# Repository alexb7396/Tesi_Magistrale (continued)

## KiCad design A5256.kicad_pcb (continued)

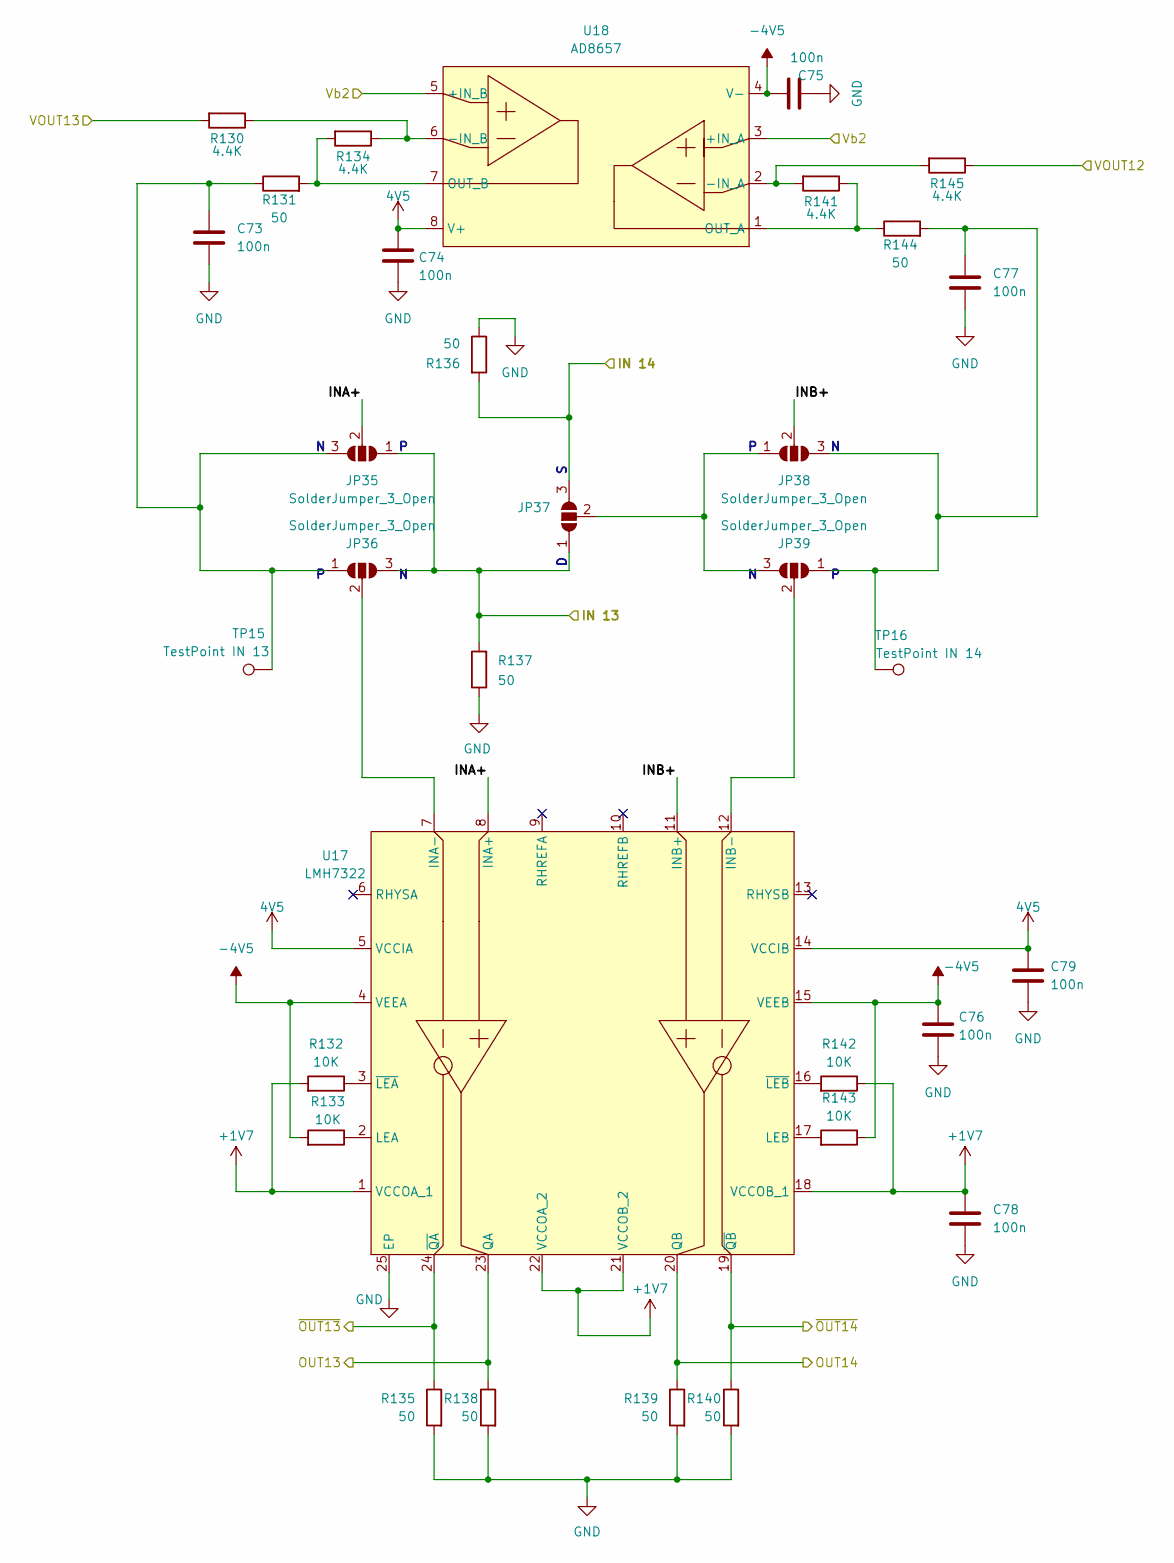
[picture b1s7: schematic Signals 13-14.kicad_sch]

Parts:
C73, C74, C75, C76, C77, C78, C79: 100n; C_0603_1608Metric_Pad1.08x0.95mm_HandSolder
JP35, JP36, JP37, JP38, JP39: SolderJumper_3_Open; SolderJumper-3_P1.3mm_Open_RoundedPad1.0x1.5mm_NumberLabels
R130, R134, R141, R145: 4.4K; R_0603_1608Metric_Pad0.98x0.95mm_HandSolder
R131, R135, R136, R137, R138, R139, R140, R144: 50; R_0603_1608Metric_Pad0.98x0.95mm_HandSolder
R132, R133, R142, R143: 10K; R_0603_1608Metric_Pad0.98x0.95mm_HandSolder
TP15: TestPoint IN 13; TestPoint_Pad_D1.0mm
TP16: TestPoint IN 14; TestPoint_Pad_D1.0mm
U17: LMH7322; QFN50P400X400X80-25N
U18: AD8657; SOP65P490X110-8N

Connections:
4V5: C74.1, C79.1, U17.5 (VCCIA), U17.14 (VCCIB), U18.8 (V+); also elsewhere on the board
+1V7: C78.1, R132.2, R142.1, U17.1 (VCCOA_1), U17.18 (VCCOB_1), U17.21 (VCCOB_2), U17.22 (VCCOA_2); also elsewhere on the board
-4V5: C75.1, C76.1, R133.2, R143.1, U17.4 (VEEA), U17.15 (VEEB), U18.4 (V-); also elsewhere on the board
/IN 13: JP35.1 (A), JP36.3 (B), JP37.1 (A), R137.2; also elsewhere on the board
/IN 14: JP37.3 (B), R136.2; also elsewhere on the board
/OUT13: R138.1, U17.23 (QA); also elsewhere on the board
/OUT14: R139.1, U17.20 (QB); also elsewhere on the board
/Signals 13-14/INA+: JP35.2 (C), U17.8 (INA+)
/Signals 13-14/INB+: JP38.2 (C), U17.11 (INB+)
/VOUT12: R145.1; also elsewhere on the board
/VOUT13: R130.2; also elsewhere on the board
/Vb2: U18.3 (+IN_A), U18.5 (+IN_B); also elsewhere on the board
/~OUT13: R135.1, U17.24 (~QA); also elsewhere on the board
/~OUT14: R140.1, U17.19 (~QB); also elsewhere on the board
GND: C73.2, C74.2, C75.2, C76.2, C77.2, C78.2, C79.2, R135.2, R136.1, R137.1, R138.2, R139.2, R140.2, U17.25 (EP); also elsewhere on the board
unnamed: C73.1, JP35.3 (B), JP36.1 (A), R131.1, TP15.1
unnamed: JP36.2 (C), U17.7 (INA-)
unnamed: JP37.2 (C), JP38.1 (A), JP39.3 (B)
unnamed: C77.1, JP38.3 (B), JP39.1 (A), R144.2, TP16.1
unnamed: JP39.2 (C), U17.12 (INB-)
unnamed: R133.1, U17.2 (LEA)
unnamed: R143.2, U17.17 (LEB)
unnamed: R132.1, U17.3 (~LEA)
unnamed: R142.2, U17.16 (~LEB)
unnamed: R141.2, R145.2, U18.2 (-IN_A)
unnamed: R130.1, R134.1, U18.6 (-IN_B)
unnamed: R141.1, R144.1, U18.1 (OUT_A)
unnamed: R131.2, R134.2, U18.7 (OUT_B)

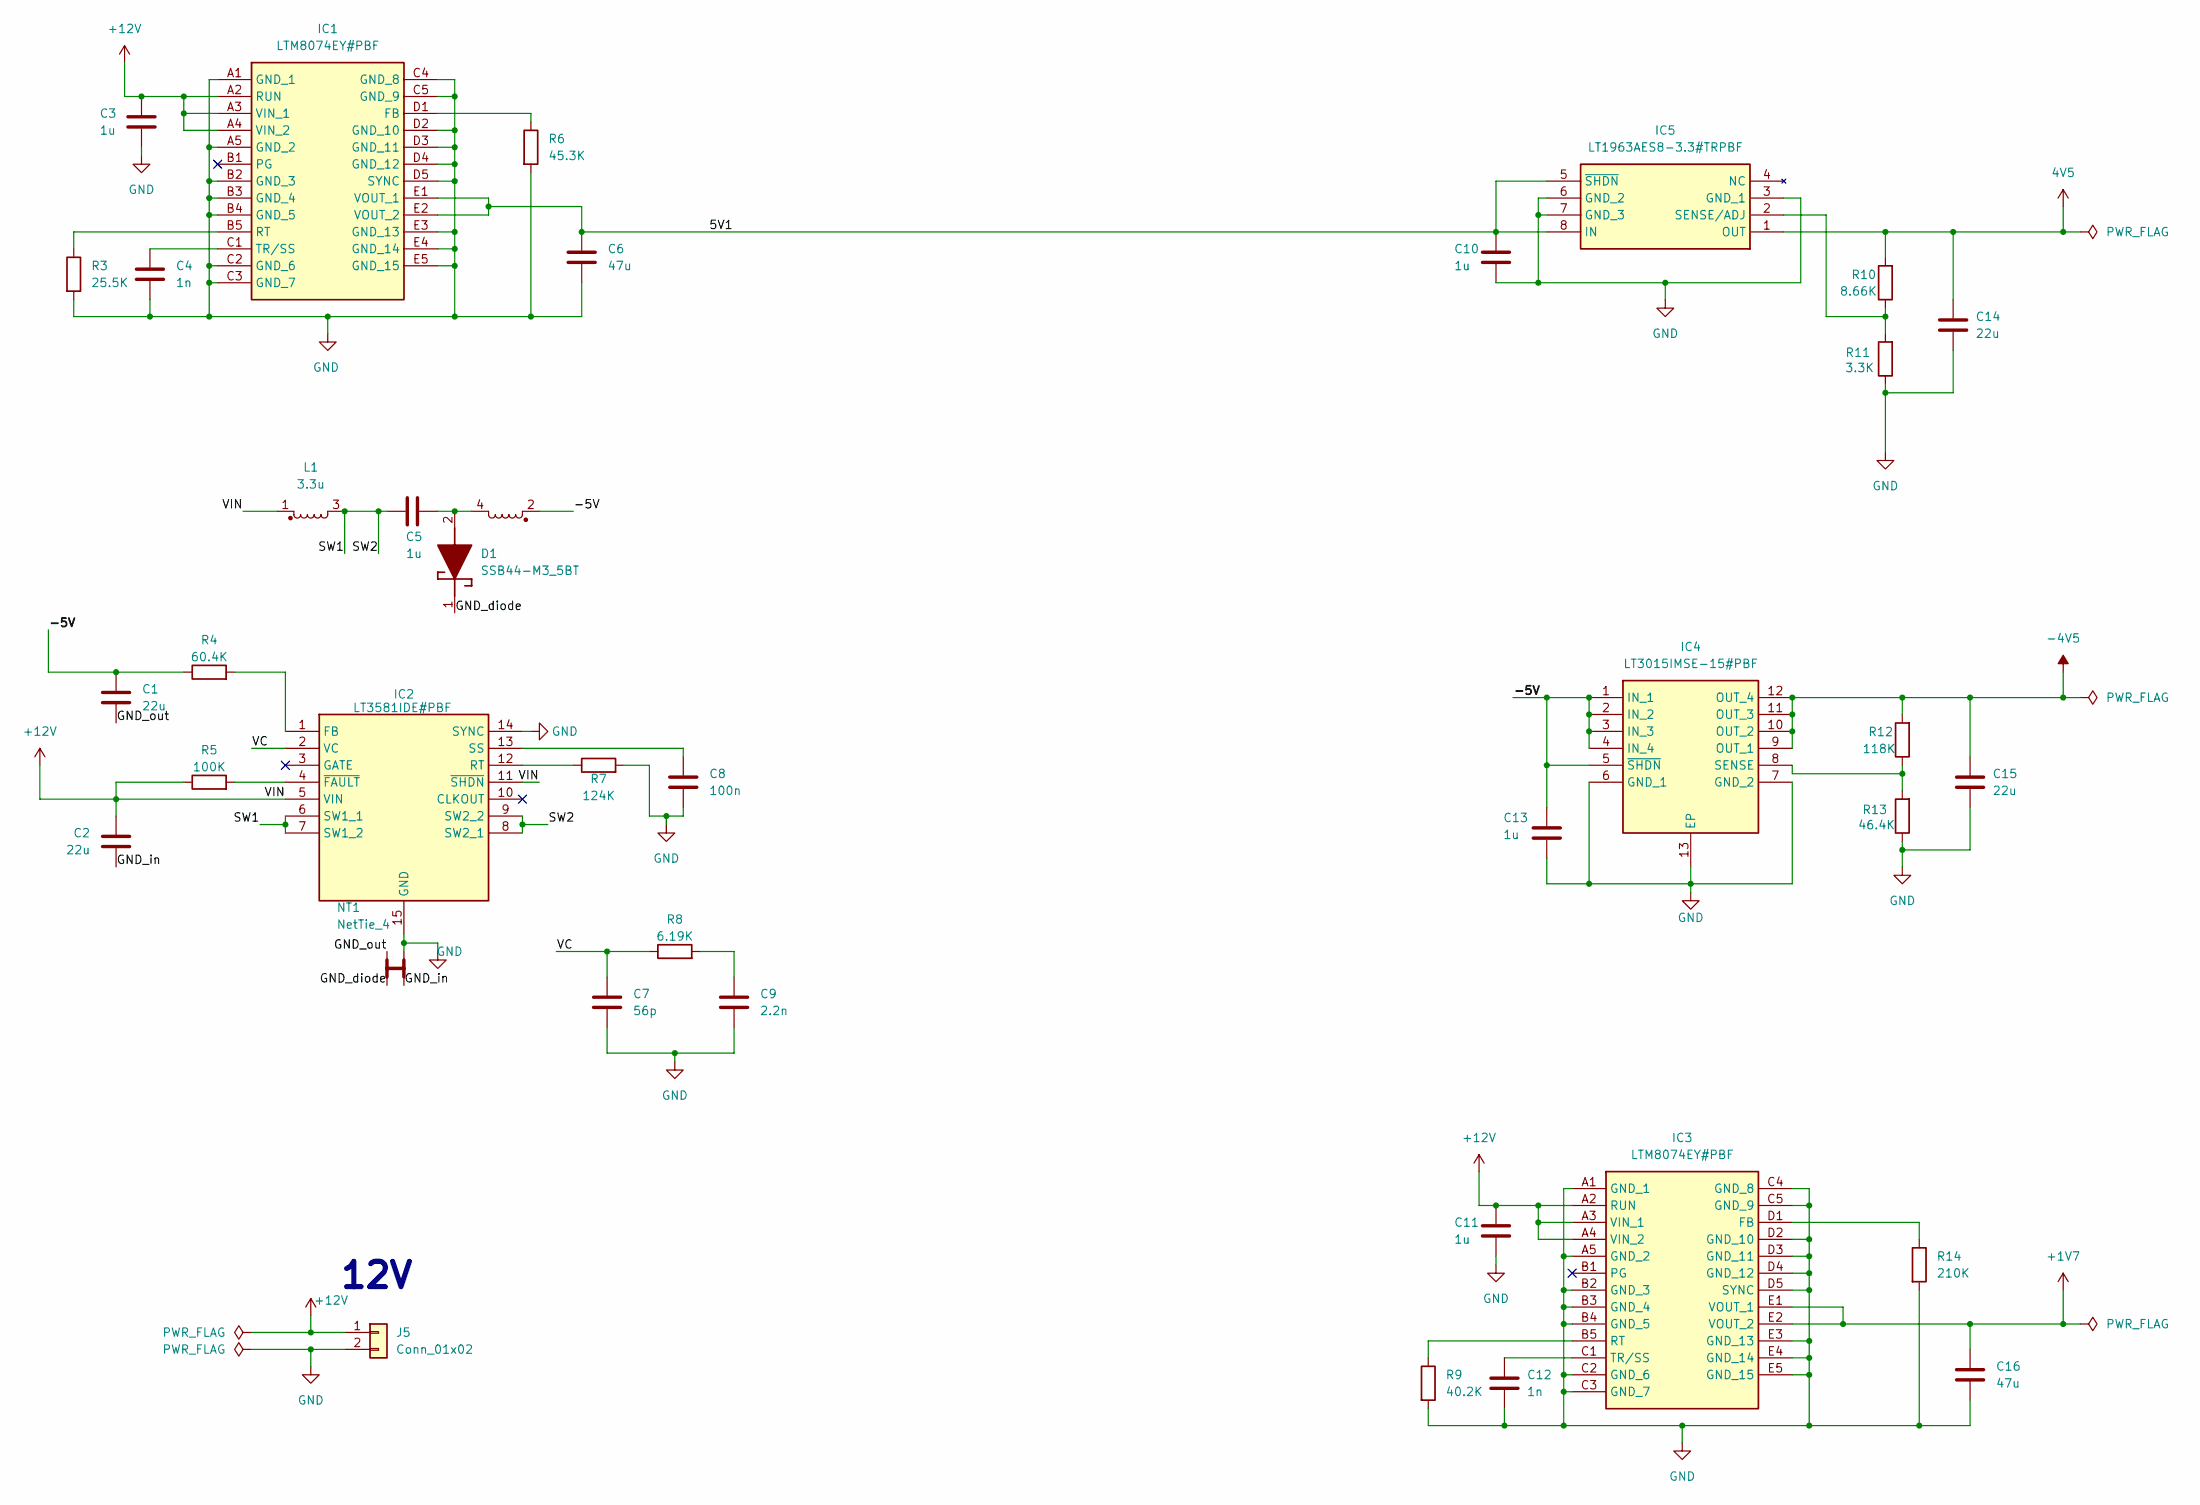
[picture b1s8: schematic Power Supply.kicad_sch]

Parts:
C1, C2: 22u; C_1210_3225Metric_Pad1.33x2.70mm_HandSolder
C3, C10, C11, C13: 1u; C_0603_1608Metric_Pad1.08x0.95mm_HandSolder
C4, C12: 1n; C_0603_1608Metric_Pad1.08x0.95mm_HandSolder
C5: 1u; C_1206_3216Metric_Pad1.33x1.80mm_HandSolder
C6, C16: 47u; C_0805_2012Metric_Pad1.18x1.45mm_HandSolder
C7: 56p; C_0603_1608Metric_Pad1.08x0.95mm_HandSolder
C8: 100n; C_0603_1608Metric_Pad1.08x0.95mm_HandSolder
C9: 2.2n; C_0603_1608Metric_Pad1.08x0.95mm_HandSolder
C14, C15: 22u; C_0805_2012Metric_Pad1.18x1.45mm_HandSolder
D1: SSB44-M3_5BT; DIOM5436X244N; Mouser Part Number 78-SSB44-M35BT
IC1, IC3: LTM8074EY#PBF; BGA25C65P5X5_400X400X198; Manufacturer_Part_Number LTM8074EY#PBF; Mouser Part Number 584-LTM8074EY#PBF
IC2: LT3581IDE#PBF; SON50P300X400X80-15N-D; Mouser Part Number 584-LT3581IDE#PBF
IC4: LT3015IMSE-15#PBF; SOP65P490X110-13N; Manufacturer_Part_Number LT3015IMSE-15#PBF; Mouser Part Number 584-LT3015IMSE-15PBF
IC5: LT1963AES8-3.3#TRPBF; SOIC127P599X175-8N; Manufacturer_Part_Number LT1963AES8-3.3#TRPBF; Mouser Part Number 584-1963AES8-3.3TPF
J5: Conn_01x02; 1725656
L1: 3.3u; MSD7342332MLC
NT1: NetTie_4; NetTie-4_SMD_Pad0.5mm
R3: 25.5K; R_0603_1608Metric_Pad0.98x0.95mm_HandSolder
R4: 60.4K; R_0603_1608Metric_Pad0.98x0.95mm_HandSolder
R5: 100K; R_0603_1608Metric_Pad0.98x0.95mm_HandSolder
R6: 45.3K; R_0603_1608Metric_Pad0.98x0.95mm_HandSolder
R7: 124K; R_0603_1608Metric_Pad0.98x0.95mm_HandSolder
R8: 6.19K; R_0603_1608Metric_Pad0.98x0.95mm_HandSolder
R9: 40.2K; R_0603_1608Metric_Pad0.98x0.95mm_HandSolder
R10: 8.66K; R_0603_1608Metric_Pad0.98x0.95mm_HandSolder
R11: 3.3K; R_0603_1608Metric_Pad0.98x0.95mm_HandSolder
R12: 118K; R_0603_1608Metric_Pad0.98x0.95mm_HandSolder
R13: 46.4K; R_0603_1608Metric_Pad0.98x0.95mm_HandSolder
R14: 210K; R_0603_1608Metric_Pad0.98x0.95mm_HandSolder

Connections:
4V5: C14.1, IC5.1 (OUT), R10.2; also elsewhere on the board
+1V7: C16.1, IC3.E1 (VOUT_1), IC3.E2 (VOUT_2); also elsewhere on the board
+12V: C2.1, C3.1, C11.1, IC1.A2 (RUN), IC1.A3 (VIN_1), IC1.A4 (VIN_2), IC2.5 (VIN), IC2.11 (~SHDN), IC3.A2 (RUN), IC3.A3 (VIN_1), IC3.A4 (VIN_2), J5.1, L1.1, R5.1
-4V5: C15.1, IC4.9 (OUT_1), IC4.10 (OUT_2), IC4.11 (OUT_3), IC4.12 (OUT_4), R12.2; also elsewhere on the board
/Power Supply/5V1: C6.1, C10.1, IC1.E1 (VOUT_1), IC1.E2 (VOUT_2), IC5.5 (~SHDN), IC5.8 (IN)
/Power Supply/-5V: C1.1, C13.1, IC4.1 (IN_1), IC4.2 (IN_2), IC4.3 (IN_3), IC4.4 (IN_4), IC4.5 (~SHDN), L1.2, R4.1
/Power Supply/GND_diode: D1.1 (K), NT1.1
/Power Supply/GND_in: C2.2, NT1.3
/Power Supply/GND_out: C1.2, NT1.2
/Power Supply/SW1: C5.2, IC2.6 (SW1_1), IC2.7 (SW1_2), IC2.8 (SW2_1), IC2.9 (SW2_2), L1.3
/Power Supply/VC: C7.2, IC2.2 (VC), R8.1
GND: C3.2, C4.2, C6.2, C7.1, C8.2, C9.2, C10.2, C11.2, C12.2, C13.2, C14.2, C15.2, C16.2, IC1.A1 (GND_1), IC1.A5 (GND_2), IC1.B2 (GND_3), IC1.B3 (GND_4), IC1.B4 (GND_5), IC1.C2 (GND_6), IC1.C3 (GND_7), IC1.C4 (GND_8), IC1.C5 (GND_9), IC1.D2 (GND_10), IC1.D3 (GND_11), IC1.D4 (GND_12), IC1.D5 (SYNC), IC1.E3 (GND_13), IC1.E4 (GND_14), IC1.E5 (GND_15), IC2.14 (SYNC), IC2.15 (GND), IC3.A1 (GND_1), IC3.A5 (GND_2), IC3.B2 (GND_3), IC3.B3 (GND_4), IC3.B4 (GND_5), IC3.C2 (GND_6), IC3.C3 (GND_7), IC3.C4 (GND_8), IC3.C5 (GND_9), IC3.D2 (GND_10), IC3.D3 (GND_11), IC3.D4 (GND_12), IC3.D5 (SYNC), IC3.E3 (GND_13), IC3.E4 (GND_14), IC3.E5 (GND_15), IC4.6 (GND_1), IC4.7 (GND_2), IC4.13 (EP), IC5.3 (GND_1), IC5.6 (GND_2), IC5.7 (GND_3), J5.2, NT1.4, R3.2, R6.2, R7.2, R9.2, R11.1, R13.1, R14.2; also elsewhere on the board
unnamed: C9.1, R8.2
unnamed: C5.1, D1.2 (A), L1.4
unnamed: IC1.D1 (FB), R6.1
unnamed: IC1.B5 (RT), R3.1
unnamed: C4.1, IC1.C1 (TR/SS)
unnamed: IC2.1 (FB), R4.2
unnamed: IC2.12 (RT), R7.1
unnamed: C8.1, IC2.13 (SS)
unnamed: IC2.4 (~FAULT), R5.2
unnamed: IC3.D1 (FB), R14.1
unnamed: IC3.B5 (RT), R9.1
unnamed: C12.1, IC3.C1 (TR/SS)
unnamed: IC4.8 (SENSE), R12.1, R13.2
unnamed: IC5.2 (SENSE/ADJ), R10.1, R11.2

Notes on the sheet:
12V

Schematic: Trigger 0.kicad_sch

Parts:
C17, C18, C19, C20, C21, C22, C24, C25, C26, C27, C28, C29, C30: 100n; C_0603_1608Metric_Pad1.08x0.95mm_HandSolder
C23: 470n; C_0603_1608Metric_Pad1.08x0.95mm_HandSolder
C80: 10u; C_0603_1608Metric_Pad1.08x0.95mm_HandSolder
IC6: AD5673RBCPZ-1; QFN40P400X400X100-29N-D; Manufacturer_Part_Number AD5673RBCPZ-1; Mouser Part Number 584-AD5673RBCPZ-1
JP1, JP2, JP3, JP4: SolderJumper_3_Open; SolderJumper-3_P1.3mm_Open_RoundedPad1.0x1.5mm_NumberLabels
L2: 22u; L_0603_1608Metric_Pad1.05x0.95mm_HandSolder
R15, R16, R19, R20, R22, R24, R31, R32, R33: 50; R_0603_1608Metric_Pad0.98x0.95mm_HandSolder
R17: 3K; R_0603_1608Metric_Pad0.98x0.95mm_HandSolder
R18: 1K; R_0603_1608Metric_Pad0.98x0.95mm_HandSolder
R21, R23, R29, R30: 4.4K; R_0603_1608Metric_Pad0.98x0.95mm_HandSolder
R25, R26, R27, R28: 10K; R_0603_1608Metric_Pad0.98x0.95mm_HandSolder
TP1: TestPoint IN 0A; TestPoint_Pad_D1.0mm
TP2: TestPoint IN 0B; TestPoint_Pad_D1.0mm
U1: LTC2627IDE-1_PBF; DFN-12_DE; MANUFACTURER_PART_NUMBER ltc2627ide1
U2, U3: AD8657; SOP65P490X110-8N
U4: LMH7322; QFN50P400X400X80-25N

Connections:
4V5: C18.1, C19.1, C22.1, C27.1, C28.1, C80.1, IC6.2 (VDD), IC6.17 (~LDAC), IC6.18 (VLOGIC), IC6.20 (~RESET), JP1.1 (A), JP2.1 (A), JP3.3 (B), JP4.3 (B), U1.3 (*LDAC), U1.8 (VCC), U2.8 (V+), U3.8 (V+), U4.5 (VCCIA), U4.14 (VCCIB); also elsewhere on the board
+1V7: C25.1, R27.2, R28.1, U4.1 (VCCOA_1), U4.18 (VCCOB_1), U4.21 (VCCOB_2), U4.22 (VCCOA_2); also elsewhere on the board
-4V5: C20.1, C24.1, C26.1, R25.2, R26.1, U2.4 (V-), U3.4 (V-), U4.4 (VEEA), U4.15 (VEEB); also elsewhere on the board
/CH0/A0: IC6.4 (A0), JP4.2 (C)
/CH0/A1: IC6.5 (A1), JP2.2 (C)
/CH0/CA0: JP3.2 (C), U1.1 (CA0)
/CH0/CA1: JP1.2 (C), U1.2 (CA1)
/CH0/SCL: IC6.3 (SCL), U1.4 (SCL); also elsewhere on the board
/CH0/SDA: IC6.19 (SDA), U1.5 (SDA); also elsewhere on the board
/CH0/Vb: C23.1, R17.2, R18.2, U2.3 (+IN_A), U2.5 (+IN_B)
/IN 0: R33.2, U4.7 (INA-), U4.12 (INB-); also elsewhere on the board
/QA_CH0: R22.1, U4.23 (QA); also elsewhere on the board
/QB_CH0: R20.1, U4.20 (QB); also elsewhere on the board
/VOUT0: IC6.25 (VOUT8); also elsewhere on the board
/VOUT1: IC6.24 (VOUT9); also elsewhere on the board
/VOUT2: IC6.27 (VOUT2); also elsewhere on the board
/VOUT3: IC6.26 (VOUT3); also elsewhere on the board
/VOUT4: IC6.1 (VOUT0); also elsewhere on the board
/VOUT5: IC6.28 (VOUT1); also elsewhere on the board
/VOUT6: IC6.7 (VOUT7); also elsewhere on the board
/VOUT7: IC6.8 (VOUT6); also elsewhere on the board
/VOUT8: IC6.9 (VOUT5); also elsewhere on the board
/VOUT9: IC6.10 (VOUT4); also elsewhere on the board
/VOUT10: IC6.13 (VOUT13); also elsewhere on the board
/VOUT11: IC6.14 (VOUT12); also elsewhere on the board
/VOUT12: IC6.22 (VOUT11); also elsewhere on the board
/VOUT13: IC6.23 (VOUT10); also elsewhere on the board
/Vb1: C21.1, R16.1, U3.3 (+IN_A), U3.5 (+IN_B); also elsewhere on the board
/Vb2: C17.1, R15.1; also elsewhere on the board
/~QA_CH0: R24.1, U4.24 (~QA); also elsewhere on the board
/~QB_CH0: R19.1, U4.19 (~QB); also elsewhere on the board
GND: C17.2, C18.2, C19.2, C20.2, C21.2, C22.2, C23.2, C24.2, C25.2, C26.2, C27.2, C28.2, C29.2, C30.2, C80.2, IC6.6 (GAIN), IC6.15 (GND_1), IC6.16 (GND_2), IC6.29 (EPAD), JP1.3 (B), JP2.3 (B), JP3.1 (A), JP4.1 (A), L2.2, R19.2, R20.2, R22.2, R24.2, R33.1, U1.6 (CA2), U1.10 (GND), U1.11 (REFLO), U1.13 (EPAD), U4.25 (EP); also elsewhere on the board
unnamed: IC6.21 (VREF), R17.1, U1.9 (REF)
unnamed: L2.1, R18.1
unnamed: R21.1, U1.12 (VOUTA)
unnamed: R30.2, U1.7 (VOUTB)
unnamed: R16.2, U2.1 (OUT_A), U2.2 (-IN_A)
unnamed: R15.2, U2.6 (-IN_B), U2.7 (OUT_B)
unnamed: R21.2, R23.1, U3.2 (-IN_A)
unnamed: R29.2, R30.1, U3.6 (-IN_B)
unnamed: R23.2, R31.1, U3.1 (OUT_A)
unnamed: R29.1, R32.1, U3.7 (OUT_B)
unnamed: C30.1, R32.2, TP2.1, U4.8 (INA+)
unnamed: C29.1, R31.2, TP1.1, U4.11 (INB+)
unnamed: R26.2, U4.2 (LEA)
unnamed: R25.1, U4.17 (LEB)
unnamed: R28.2, U4.3 (~LEA)
unnamed: R27.1, U4.16 (~LEB)

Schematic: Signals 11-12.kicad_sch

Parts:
C66, C67, C68, C69, C70, C71, C72: 100n; C_0603_1608Metric_Pad1.08x0.95mm_HandSolder
JP30, JP31, JP32, JP33, JP34: SolderJumper_3_Open; SolderJumper-3_P1.3mm_Open_RoundedPad1.0x1.5mm_NumberLabels
R114, R118, R125, R129: 4.4K; R_0603_1608Metric_Pad0.98x0.95mm_HandSolder
R115, R119, R120, R121, R122, R123, R124, R128: 50; R_0603_1608Metric_Pad0.98x0.95mm_HandSolder
R116, R117, R126, R127: 10K; R_0603_1608Metric_Pad0.98x0.95mm_HandSolder
TP13: TestPoint IN 11; TestPoint_Pad_D1.0mm
TP14: TestPoint IN 12; TestPoint_Pad_D1.0mm
U15: LMH7322; QFN50P400X400X80-25N
U16: AD8657; SOP65P490X110-8N

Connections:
4V5: C67.1, C72.1, U15.5 (VCCIA), U15.14 (VCCIB), U16.8 (V+); also elsewhere on the board
+1V7: C71.1, R116.2, R126.1, U15.1 (VCCOA_1), U15.18 (VCCOB_1), U15.21 (VCCOB_2), U15.22 (VCCOA_2); also elsewhere on the board
-4V5: C68.1, C69.1, R117.2, R127.1, U15.4 (VEEA), U15.15 (VEEB), U16.4 (V-); also elsewhere on the board
/IN 11: JP30.1 (A), JP31.3 (B), JP32.1 (A), R121.2; also elsewhere on the board
/IN 12: JP32.3 (B), R120.2; also elsewhere on the board
/OUT11: R122.1, U15.23 (QA); also elsewhere on the board
/OUT12: R123.1, U15.20 (QB); also elsewhere on the board
/Signals 11-12/INA+: JP30.2 (C), U15.8 (INA+)
/Signals 11-12/INB+: JP33.2 (C), U15.11 (INB+)
/VOUT10: R129.1; also elsewhere on the board
/VOUT11: R114.2; also elsewhere on the board
/Vb2: U16.3 (+IN_A), U16.5 (+IN_B); also elsewhere on the board
/~OUT11: R119.1, U15.24 (~QA); also elsewhere on the board
/~OUT12: R124.1, U15.19 (~QB); also elsewhere on the board
GND: C66.2, C67.2, C68.2, C69.2, C70.2, C71.2, C72.2, R119.2, R120.1, R121.1, R122.2, R123.2, R124.2, U15.25 (EP); also elsewhere on the board
unnamed: C66.1, JP30.3 (B), JP31.1 (A), R115.1, TP13.1
unnamed: JP31.2 (C), U15.7 (INA-)
unnamed: JP32.2 (C), JP33.1 (A), JP34.3 (B)
unnamed: C70.1, JP33.3 (B), JP34.1 (A), R128.2, TP14.1
unnamed: JP34.2 (C), U15.12 (INB-)
unnamed: R117.1, U15.2 (LEA)
unnamed: R127.2, U15.17 (LEB)
unnamed: R116.1, U15.3 (~LEA)
unnamed: R126.2, U15.16 (~LEB)
unnamed: R125.2, R129.2, U16.2 (-IN_A)
unnamed: R114.1, R118.1, U16.6 (-IN_B)
unnamed: R125.1, R128.1, U16.1 (OUT_A)
unnamed: R115.2, R118.2, U16.7 (OUT_B)

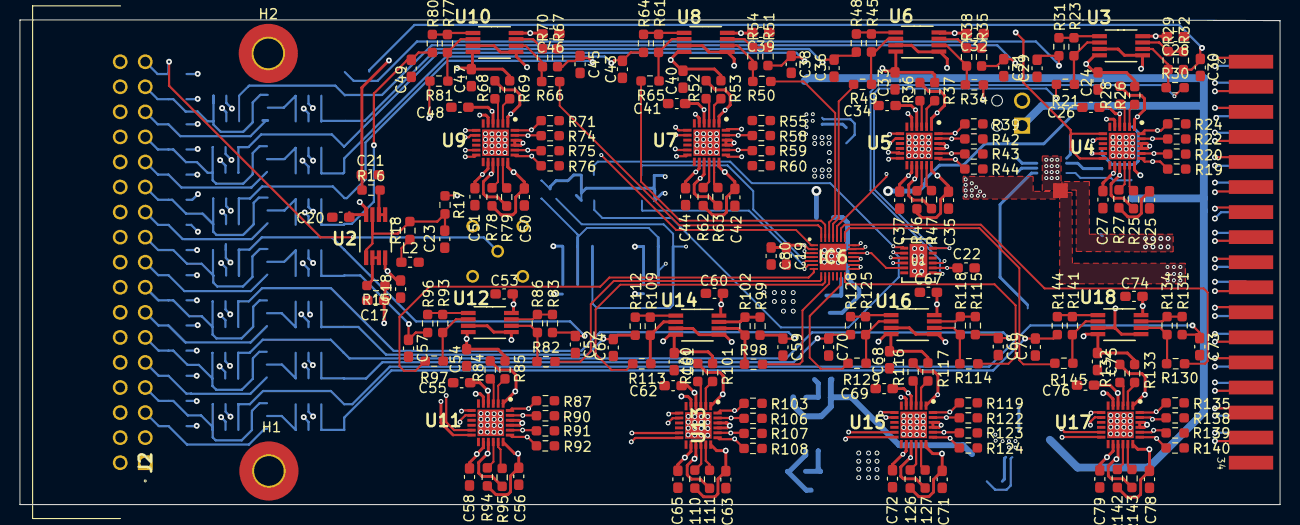
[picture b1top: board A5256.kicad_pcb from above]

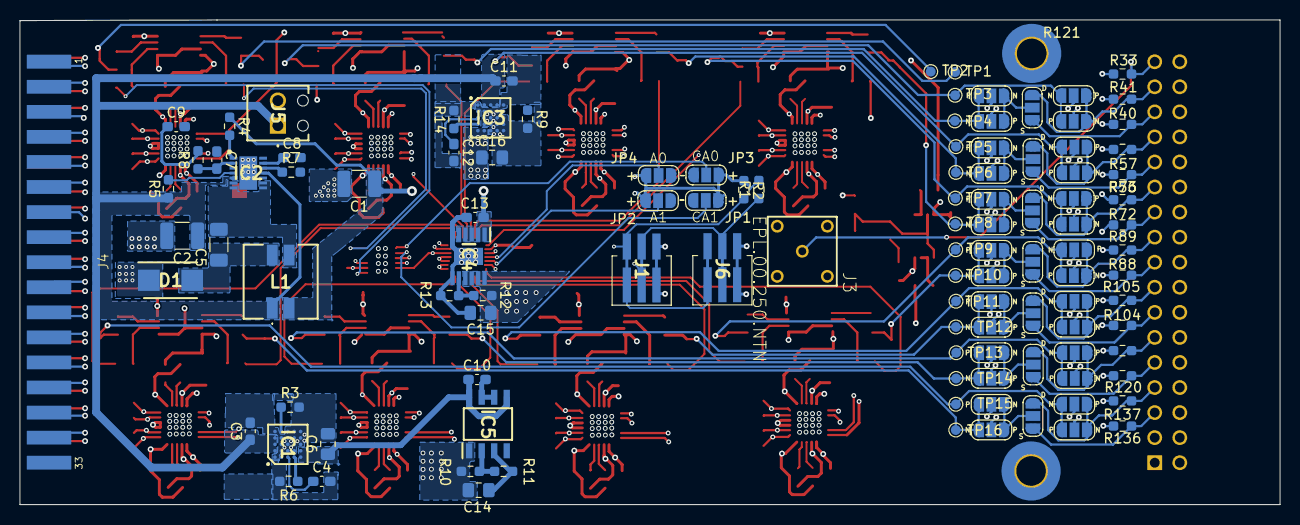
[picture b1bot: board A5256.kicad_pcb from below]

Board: 6 copper layers, 127.7 x 49.1 mm, 316 parts (112 on the bottom side), 217 nets.

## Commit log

2024-12-16 primo commit tesi
2024-12-16 quasi terminato il back
2024-12-22 fatto piano di power
2024-12-22 messo le masse back and front
2024-12-23 posizionato riferimenti in modo corretto
2024-12-28 modifiche per rispettare vincoli azienda
2025-01-05 terminato pcb e aggiunto script GUI
2025-01-09 completata gui
2025-02-13 versione finale
2025-02-19 modificato pad esposti
2025-03-06 aggiunto file sketch ardunio
